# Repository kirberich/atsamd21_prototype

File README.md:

# ATSAMD21 Prototype board

This is a first prototype of a simple, debuggable, Arduino-Nano-ish development board. It's unlikely to be useful to anyone, it's just a proving ground for building more useful boards in future revisions once this one is shown to work.

For an actual development board, I'd recommend buying Adafruit's Feather M0 Express. The MCU package in this eagle file is taken from that board.

https://github.com/adafruit/Adafruit-Feather-M0-Express-PCB

https://www.adafruit.com/product/3403

In the UK: https://shop.pimoroni.com/products/adafruit-feather-m0-express-designed-for-circuitpython-atsamd21-cortex-m0?variant=40768798794&gclid=EAIaIQobChMIxtmcoaWn4AIV7ZXtCh1CmgXREAQYASABEgJSj_D_BwE

Licensed under Creative Commons CC BY-SA 4.0: https://creativecommons.org/licenses/by-sa/4.0/

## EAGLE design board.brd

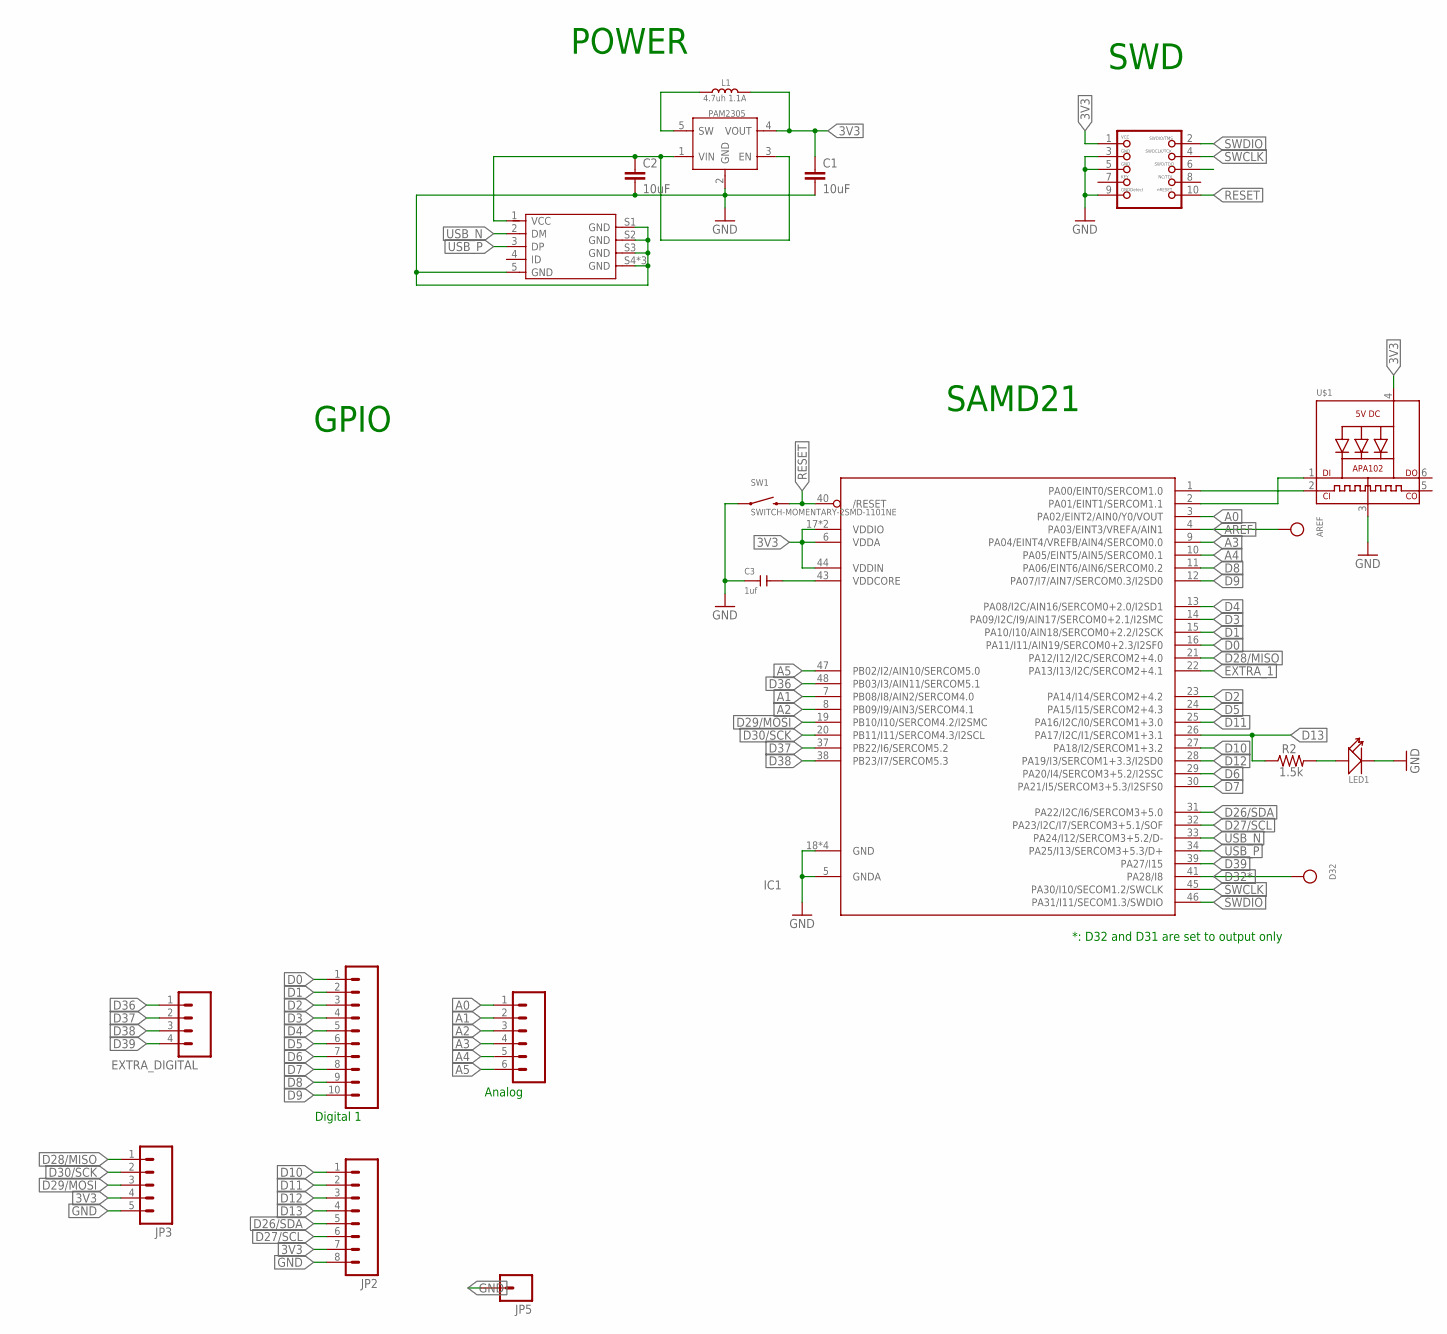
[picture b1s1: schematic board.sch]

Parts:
ANALOG: 6p-2.54; 1X06_NO_SILK
AREF: TESTPOINTROUND1MM; TESTPOINT_ROUND_1MM
C1, C2: 10uF; 0805
C3: 1uf; C0805
D32: TESTPOINTROUND1MM; TESTPOINT_ROUND_1MM
EXTRA_DIGITAL: M04NO_SILK_ALL_ROUND; 1X04_NO_SILK_ALL_ROUND
IC1: MICROBUILDER_ATSAMD21G_QFN; MICROBUILDER_TQFN48_7MM
JP1: M10NO_SILK_PTH_FEMALE; 1X10_NO_SILK
JP2: M08NO_SILK_FEMALE_PTH; 1X08_NO_SILK
JP3: M05NO_SILK; 1X05_NO_SILK
JP5: M01PTH_NO_SILK_YES_STOP; 1X01_NO_SILK
JTAG1: JTAG-CORTEXM3; 2X05_1.27MM_SMT
L1: 4.7uh 1.1A; L1008
LED1: RED-0805; LED-0805
PAM2305: XC6204B332MR-SOT23-5; SOT-23-5
R2: 1.5k; 0805
SW1: SWITCH-MOMENTARY-2SMD-1101NE; TACTILE-SWITCH-1101NE
U$1: MICROBUILDER_APA102
USB2: ST-USB-001G; MICRO-USB5+4P-SMD-0.65-B

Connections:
3V3: C1.1, IC1.6 (VDDA), IC1.17 (VDDIO), IC1.36 (VDDIO), IC1.44 (VDDIN), JP2.7, JP3.4, JTAG1.1, L1.2, PAM2305.4 (VOUT), U$1.4 (VDD)
A0: ANALOG.1, IC1.3 (PA02/EINT2/AIN0/Y0/VOUT)
A1: ANALOG.2, IC1.7 (PB08/I8/AIN2/SERCOM4.0)
A2: ANALOG.3, IC1.8 (PB09/I9/AIN3/SERCOM4.1)
A3: ANALOG.4, IC1.9 (PA04/EINT4/VREFB/AIN4/SERCOM0.0)
A4: ANALOG.5, IC1.10 (PA05/EINT5/AIN5/SERCOM0.1)
A5: ANALOG.6, IC1.47 (PB02/I2/AIN10/SERCOM5.0)
AREF: AREF.P$1, IC1.4 (PA03/EINT3/VREFA/AIN1)
D0: IC1.16 (PA11/I11/AIN19/SERCOM0+2.3/I2SF0), JP1.1
D1: IC1.15 (PA10/I10/AIN18/SERCOM0+2.2/I2SCK), JP1.2
D2: IC1.23 (PA14/I14/SERCOM2+4.2), JP1.3
D3: IC1.14 (PA09/I2C/I9/AIN17/SERCOM0+2.1/I2SMC), JP1.4
D4: IC1.13 (PA08/I2C/AIN16/SERCOM0+2.0/I2SD1), JP1.5
D5: IC1.24 (PA15/I15/SERCOM2+4.3), JP1.6
D6: IC1.29 (PA20/I4/SERCOM3+5.2/I2SSC), JP1.7
D7: IC1.30 (PA21/I5/SERCOM3+5.3/I2SFS0), JP1.8
D8: IC1.11 (PA06/EINT6/AIN6/SERCOM0.2), JP1.9
D9: IC1.12 (PA07/I7/AIN7/SERCOM0.3/I2SD0), JP1.10
D10: IC1.27 (PA18/I2/SERCOM1+3.2), JP2.1
D11: IC1.25 (PA16/I2C/I0/SERCOM1+3.0), JP2.2
D12: IC1.28 (PA19/I3/SERCOM1+3.3/I2SD0), JP2.3
D13: IC1.26 (PA17/I2C/I1/SERCOM1+3.1), JP2.4, R2.1
D26/SDA: IC1.31 (PA22/I2C/I6/SERCOM3+5.0), JP2.5
D27/SCL: IC1.32 (PA23/I2C/I7/SERCOM3+5.1/SOF), JP2.6
D28/MISO: IC1.21 (PA12/I12/I2C/SERCOM2+4.0), JP3.1
D29/MOSI: IC1.19 (PB10/I10/SERCOM4.2/I2SMC), JP3.3
D30/SCK: IC1.20 (PB11/I11/SERCOM4.3/I2SCL), JP3.2
D32*: D32.P$1, IC1.41 (PA28/I8)
D36: EXTRA_DIGITAL.1, IC1.48 (PB03/I3/AIN11/SERCOM5.1)
D37: EXTRA_DIGITAL.2, IC1.37 (PB22/I6/SERCOM5.2)
D38: EXTRA_DIGITAL.3, IC1.38 (PB23/I7/SERCOM5.3)
D39: EXTRA_DIGITAL.4, IC1.39 (PA27/I15)
D40: IC1.1 (PA00/EINT0/SERCOM1.0), U$1.2 (CKI)
D41: IC1.2 (PA01/EINT1/SERCOM1.1), U$1.1 (DI)
EXTRA_1: IC1.22 (PA13/I13/I2C/SERCOM2+4.1)
GND: C1.2, C2.2, C3.1, IC1.5 (GNDA), IC1.18 (GND), IC1.35 (GND), IC1.42 (GND), IC1.GND, JP2.8, JP3.5, JP5.1, JTAG1.3, JTAG1.5, JTAG1.9, LED1.-, PAM2305.2 (GND), SW1.1, U$1.3 (GND), USB2.5 (GND), USB2.S1 (GND), USB2.S2 (GND), USB2.S3 (GND), USB2.S4 (GND), USB2.S5 (GND), USB2.S6 (GND)
LED: LED1.+, R2.2
unnamed: L1.1, PAM2305.5 (SW)
unnamed: C3.2, IC1.43 (VDDCORE)
RESET: IC1.40 (/RESET), JTAG1.10, SW1.2
SWCLK: IC1.45 (PA30/I10/SECOM1.2/SWCLK), JTAG1.4
SWDIO: IC1.46 (PA31/I11/SECOM1.3/SWDIO), JTAG1.2
USB_N: IC1.33 (PA24/I12/SERCOM3+5.2/D-), USB2.2 (DM)
USB_P: IC1.34 (PA25/I13/SERCOM3+5.3/D+), USB2.3 (DP)
VBAT: C2.1, PAM2305.1 (VIN), PAM2305.3 (EN), USB2.1 (VCC)

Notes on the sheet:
POWER
*: D32 and D31 are set to output only
Analog
SWD
SAMD21
GPIO
Digital 1

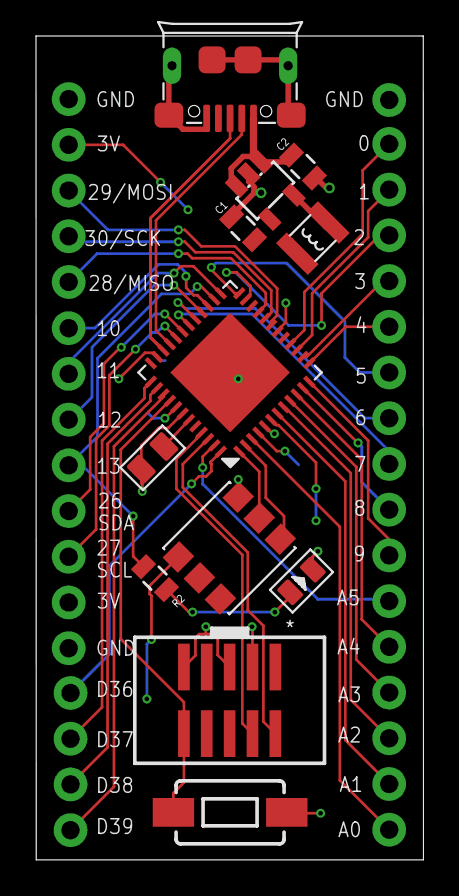
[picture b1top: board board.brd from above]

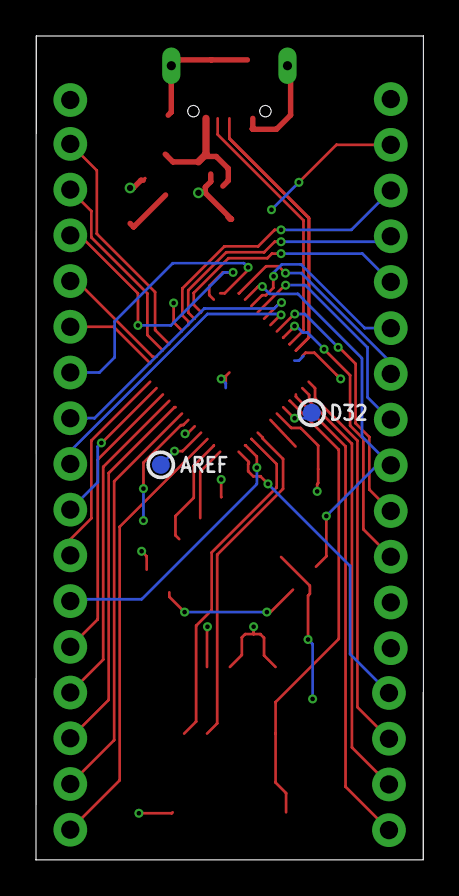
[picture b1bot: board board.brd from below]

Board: 2 copper layers, 21.5 x 45.8 mm, 20 parts (2 on the bottom side), 44 nets.

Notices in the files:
parts and their libraries:
SparkFun-Capacitors: Licensing: Creative Commons ShareAlike 4.0 International - https://creativecommons.org/licenses/by-sa/4.0
microbuilder: This work is placed in the public domain, and may be freely used for commercial and non-commercial work with the following conditions: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
